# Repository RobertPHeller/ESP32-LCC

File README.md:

# ESP32-LCC

This is a collection of Model Railroad open hardware and open source projects,
using LCC /  OpenMRNIDF, for the ESP32 family of MCUs

These projects were created using Kicad 2013.06.11
(https://launchpad.net/kicad) under CentOS 6 and Kicad 4.0.7 under Ubuntu
18.04. Each subdirectory is one project, and contains a schematic and PCB
design or contains a program for one (or more) projects. There is also
software for the boards using OpenMRNIDF (C++ library for OpenLCB/LCC) for these
projects.

There is a README in each project dir.

1. [ESP32-16LedDriver](https://github.com/RobertPHeller/RPi-RRCircuits/tree/master/ESP32-16LedDriver)

    > 16 on/off LED Driver board using a MCP23017.

1. [ESP32-16PWMLedDriver](https://github.com/RobertPHeller/RPi-RRCircuits/tree/master/ESP32-16PWMLedDriver)

    > 16 LED PWM driver board using a PCA9685.

1. [ESP32-16xDCCOD](https://github.com/RobertPHeller/RPi-RRCircuits/tree/master/ESP32-16xDCCOD)

    > Backplane for up to 16 DCCOD_SMD's using a ESP32 MCU.  Meant as a thought 
    > experiment to see what this would cost, etc.

1. [ESP32-D0WD-V3-MultiFunctionOpenMRNIDF](https://github.com/RobertPHeller/RPi-RRCircuits/tree/master/ESP32-D0WD-V3-MultiFunctionOpenMRNIDF)

    > 

1. [ESP32-HalfSiding](https://github.com/RobertPHeller/RPi-RRCircuits/tree/master/ESP32-HalfSiding)

    > First draft of a ESP32 HalfSiding node using a MCP23017 on/off signal lamps.

1. [ESP32-MultiFunction](https://github.com/RobertPHeller/RPi-RRCircuits/tree/master/ESP32-MultiFunction)

    > This is a circuit board that supports an ESP32 Dev Kit board or TTGO-T1 board
    > to manage a range of possible interlocking plants or other model railroad
    > situations. It contains four stall motor drivers with point sense, four CT
    > Coil type occupancy detectors, four Schmitt-Trigger inputs (for push buttons),
    > four driver outputs, and 16 PWM LED drivers.

1. [ESP32-PWMHalfSiding](https://github.com/RobertPHeller/RPi-RRCircuits/tree/master/ESP32-PWMHalfSiding)

    > This is a circuit board that supports an ESP32 Dev Kit board or TTGO-T1 board 
    > to manage one half (one end) of a siding.  This board can also be used to 
    > manage two bi-directional single track ABS blocks or one bi-directional dual 
    > track ABS block.  There are other trackwork cases this board can handle as 
    > well.  

1. [ESP32-PWMHalfSidingSMD](https://github.com/RobertPHeller/RPi-RRCircuits/tree/master/ESP32-PWMHalfSidingSMD)

    > This is a circuit board that supports an ESP32 Dev Kit board or TTGO-T1 board 
    > to manage one half (one end) of a siding.  This board can also be used to 
    > manage two bi-directional single track ABS blocks or one bi-directional dual 
    > track ABS block.  There are other trackwork cases this board can handle as 
    > well.  

1. [ESP32-S3-MultiFunction](https://github.com/RobertPHeller/RPi-RRCircuits/tree/master/ESP32-S3-MultiFunction)

    > This is a LCC node circuit board that is based around an Espressif ESP32-S3FN8
    > MCU to manage and operate a collection of model railroad sensors and
    > actuators. 

1. [ESP32-S3-MultiFunctionOpenMRNIDF](https://github.com/RobertPHeller/RPi-RRCircuits/tree/master/ESP32-S3-MultiFunctionOpenMRNIDF)

    > 

1. [ESP32_mini_KiCad_Library](https://github.com/RobertPHeller/RPi-RRCircuits/tree/master/ESP32_mini_KiCad_Library)

    > KiCad symbol and footprint for the ESP32 Mini, the ESP32 clone of the Wemos D1 mini with more pins and more power!
    > There is some info on the boards [here](https://www.reddit.com/r/esp8266/comments/a93raj/wemos_ttgo_mini_d1_esp32/). It seems to be a Wemos clone, but is def. not made by them. I really like the boards for the small size and cheap price while giving me the power of an ESP32 and much more IO compared to the Wemos D1 mini.

1. [ESP32ABSBoard](https://github.com/RobertPHeller/RPi-RRCircuits/tree/master/ESP32ABSBoard)

    > ESP32 ABS (Automatic Block Signal) board.  Very simple board: one block 
    > detector, 8 LED drivers.

1. [ESP32BaseBoard](https://github.com/RobertPHeller/RPi-RRCircuits/tree/master/ESP32BaseBoard)

    > ESP32 Base board.  Base starting point for a ESP32 node.

1. [ESP32MRNSketches](https://github.com/RobertPHeller/RPi-RRCircuits/tree/master/ESP32MRNSketches)

    > ESP32 Arduino / OpenMRNLite sketches for the ESP32 boards.

1. [ESP32QuadOCDect](https://github.com/RobertPHeller/RPi-RRCircuits/tree/master/ESP32QuadOCDect)

    > ESP32 Quad Occupancy Detector node.

1. [ESP32QuadSMCSense](https://github.com/RobertPHeller/RPi-RRCircuits/tree/master/ESP32QuadSMCSense)

    > ESP32 Quad Stall Motor w/ sense node.

1. [OpenMRNIDF](https://github.com/RobertPHeller/RPi-RRCircuits/tree/master/OpenMRNIDF)

    > This is an exported version of the OpenMRN library for the ESP32 which is
    > usable as an ESP-IDF component.

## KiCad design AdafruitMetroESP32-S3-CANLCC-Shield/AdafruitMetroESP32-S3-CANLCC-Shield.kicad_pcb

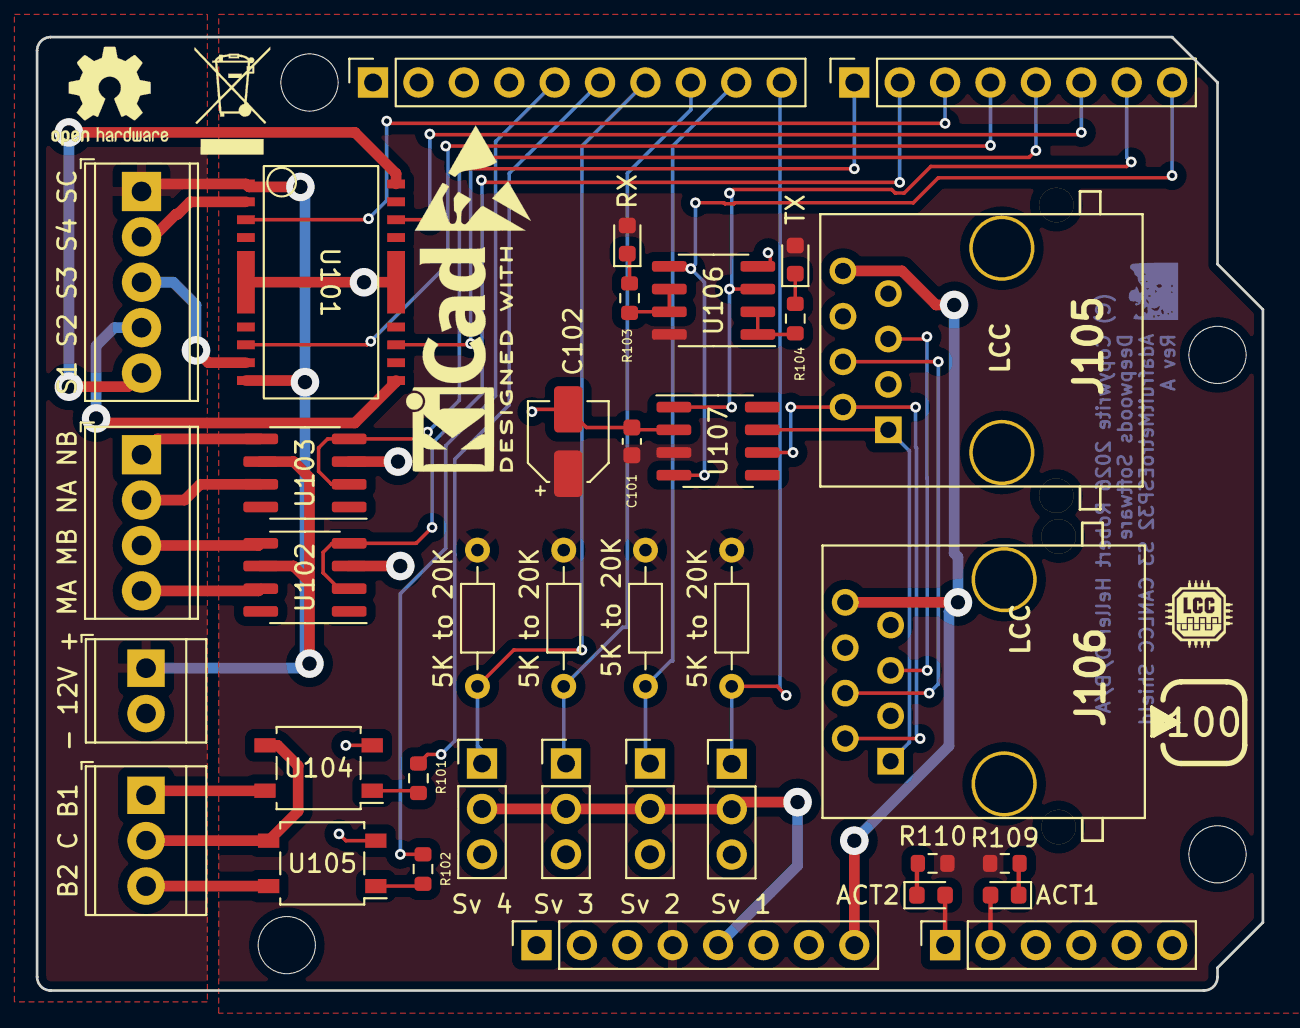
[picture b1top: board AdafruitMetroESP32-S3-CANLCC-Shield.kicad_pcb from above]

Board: 2 copper layers, 68.6 x 53.3 mm, 41 parts (0 on the bottom side), 44 nets.

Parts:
C101: .1 uf; C_0603_1608Metric
C102: 15 uf 15V; CP_Elec_4x5.7
D101: RX; LED_0603_1608Metric
D102: TX; LED_0603_1608Metric
D103: ACT1; LED_0603_1608Metric
D104: ACT2; LED_0603_1608Metric
J1: Power; PinSocket_1x08_P2.54mm_Vertical
J2: Digital/PWM; PinSocket_1x10_P2.54mm_Vertical
J3: Analog; PinSocket_1x06_P2.54mm_Vertical
J4: Digital/PWM; PinSocket_1x08_P2.54mm_Vertical
J101: MA MB NA NB; TerminalBlock_Phoenix_MPT-0,5-4-2.54_1x04_P2.54mm_Horizontal
J102: S1 S2 S3 S4 SC; TerminalBlock_Phoenix_MPT-0,5-5-2.54_1x05_P2.54mm_Horizontal
J103: - 12V +; TerminalBlock_TE_282834-2_1x02_P2.54mm_Horizontal
J104: B2 C B1; TerminalBlock_TE_282834-3_1x03_P2.54mm_Horizontal
J105, J106: LCC; RJ45_8N-S
J107: Sv 4; PinHeader_1x03_P2.54mm_Vertical
J108: Sv 3; PinHeader_1x03_P2.54mm_Vertical
J109: Sv 2; PinHeader_1x03_P2.54mm_Vertical
J110: Sv 1; PinHeader_1x03_P2.54mm_Vertical
MH1, MH2, MH3, MH4: MountingHole_3.2mm
R101, R102: 330; R_0603_1608Metric
R103, R104, R109, R110: 130; R_0603_1608Metric
R105, R106, R107, R108: 5K to 20K; R_Axial_DIN0204_L3.6mm_D1.6mm_P7.62mm_Horizontal
U101: TBD62064AFG; HSOP16-P-300-1.00
U102, U103: TC4428; SOIC-8_3.9x4.9mm_P1.27mm
U104, U105: G3VM-61VY4; SO-4_4.4x4.3mm_P2.54mm
U106: LM358; SOIC-8_3.9x4.9mm_P1.27mm
U107: TCAN332DR; SOIC-8_3.9x4.9mm_P1.27mm

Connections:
+3V3: C101.1, C102.1, D101.2 (A), D102.2 (A), J1.4, R105.1, R106.1, R107.1, R108.1, R109.1, R110.1, U106.8 (V+), U107.3 (Vcc)
+5V: J1.5, J107.2, J108.2, J109.2, J110.2
+12V: J102.1, J103.1, U101.1 (OC), U101.8 (OC), U102.6 (Vdd), U103.6 (Vdd)
/2: J4.6, U101.14 (In)
/4: J4.4, U101.6 (In)
/7: J4.1, U103.2 (IN), U103.4 (IN)
/8: J2.10, J110.1, R108.2
/12: J2.6, R101.2
/13: J2.5, R102.2
/*3: J4.5, U101.11 (In)
/*5: J4.3, U101.3 (In)
/*6: J4.2, U102.2 (IN), U102.4 (IN)
/*9: J2.9, J109.1, R107.2
/*10: J2.8, J108.1, R106.2
/*11: J2.7, J107.1, R105.2
/A0: D104.2 (A), J3.1
/A1: D103.2 (A), J3.2
/CAN_RX: J4.8, U106.5 (+), U107.4 (R)
/CAN_TX: J4.7, U106.3 (+), U107.1 (D)
GND: C101.2, C102.2, J1.6, J1.7, J2.4, J103.2, J105.3, J105.6, J105.7, J106.3, J106.6, J106.7, J107.3, J108.3, J109.3, J110.3, U101.FIN (GND), U102.3 (GND), U103.3 (GND), U104.2, U105.2, U106.4 (V-), U107.2 (GND)
unnamed: D101.1 (K), R103.1
unnamed: D102.1 (K), R104.1
unnamed: D103.1 (K), R109.2
unnamed: D104.1 (K), R110.2
unnamed: J101.1, U103.5 (Out)
unnamed: J101.2, U103.7 (Out)
unnamed: J101.3, U102.5 (Out)
unnamed: J101.4, U102.7 (Out)
unnamed: J102.2, U101.2 (Out)
unnamed: J102.3, U101.7 (Out)
unnamed: J102.4, U101.9 (Out)
unnamed: J102.5, U101.16 (Out)
unnamed: J104.1, U104.4
unnamed: J104.2, U104.3, U105.3
unnamed: J104.3, U105.4
unnamed: J105.1, J106.1, U107.7 (CANH)
unnamed: J105.2, J106.2, U107.6 (CANL)
unnamed: J105.4, J106.4
unnamed: J105.5, J106.5
unnamed: R101.1, U104.1
unnamed: R102.1, U105.1
unnamed: R103.2, U106.6 (-), U106.7
unnamed: R104.2, U106.1, U106.2 (-)
VCC: J1.8, J105.8, J106.8

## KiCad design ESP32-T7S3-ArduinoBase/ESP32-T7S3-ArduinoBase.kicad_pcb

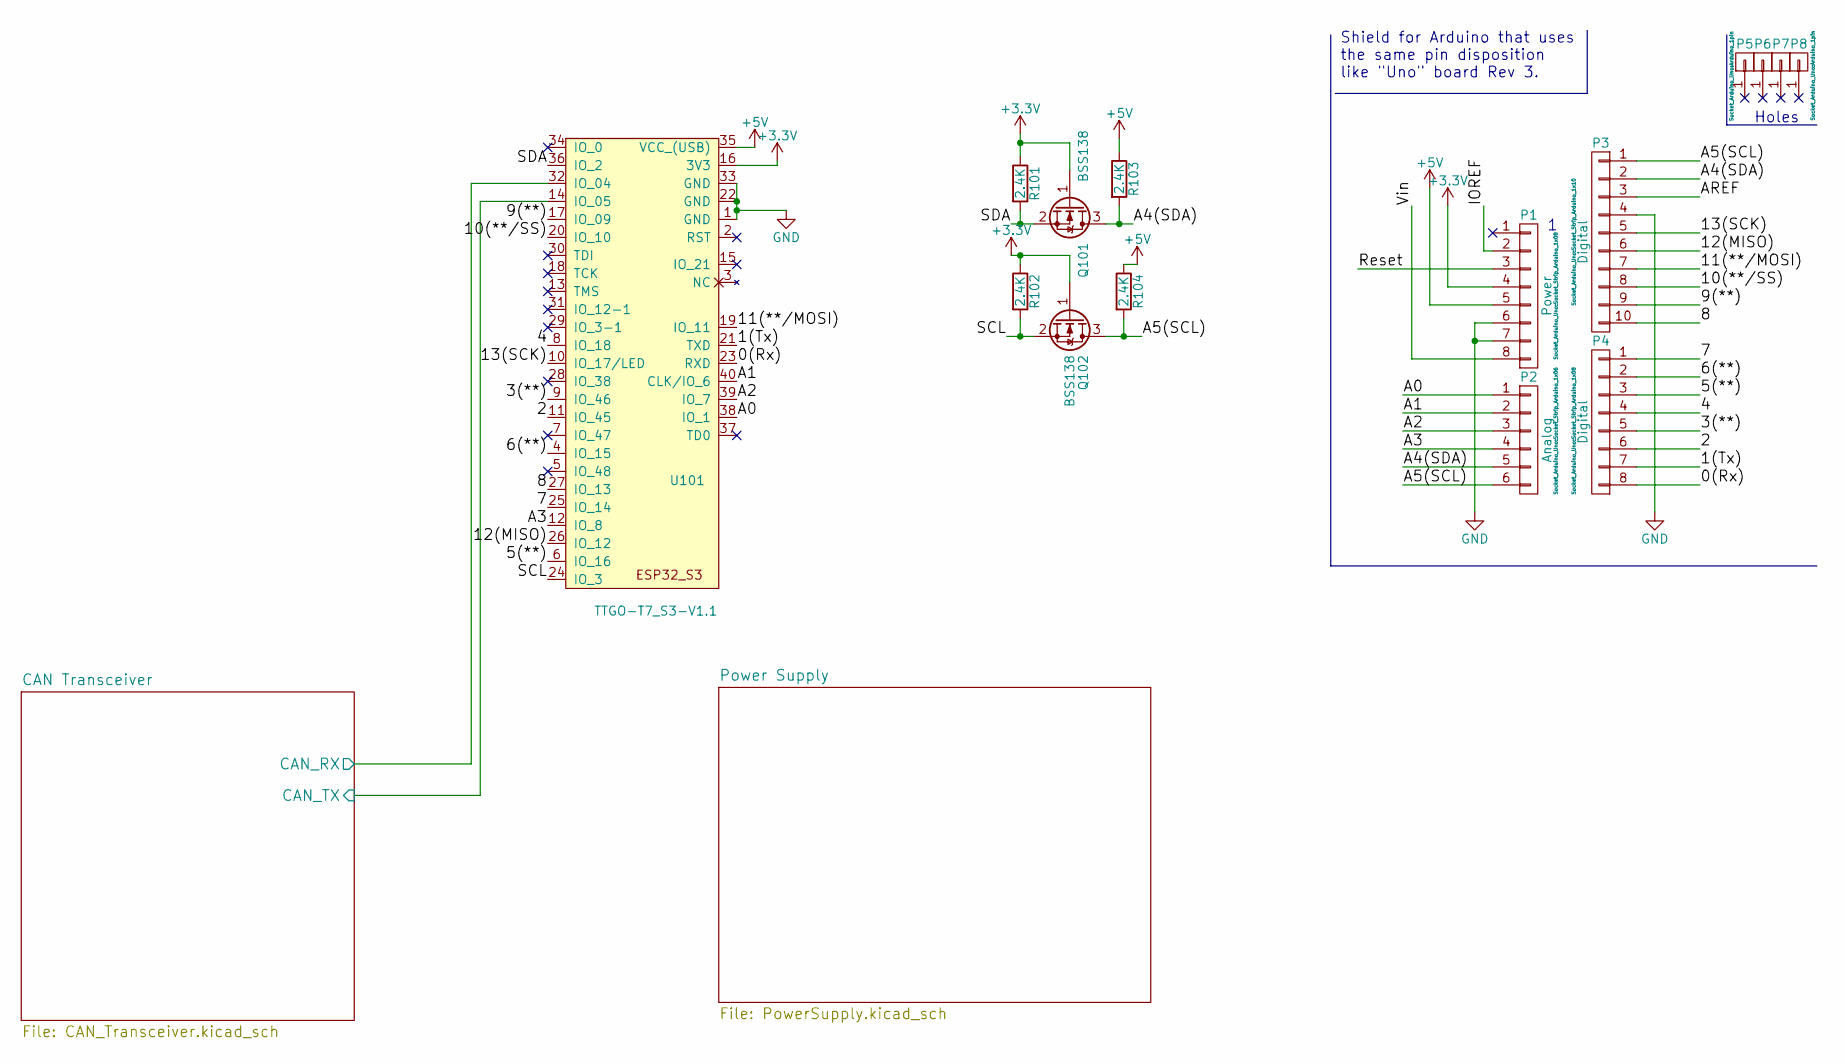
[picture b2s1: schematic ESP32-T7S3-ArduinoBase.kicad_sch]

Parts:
P1: Power; Socket_Strip_Arduino_1x08
P2: Analog; Socket_Strip_Arduino_1x06
P3: Digital; Socket_Strip_Arduino_1x10
P4: Digital; Socket_Strip_Arduino_1x08
P5, P6, P7, P8: CONN_01X01; Arduino_1pin
Q101, Q102: BSS138; SOT-23; Mouser Part Number 621-BSS138-7-F
R101, R102, R103, R104: 2.4K; R_0603
U101: TTGO-T7_S3-V1.1; ESP32_mini

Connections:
+5V: P1.5, R103.1, R104.1, U101.35 (VCC_(USB)); also elsewhere on the board
/0(Rx): P4.8, U101.23 (RXD)
/1(Tx): P4.7, U101.21 (TXD)
/2: P4.6, U101.11 (IO_45)
/3(**): P4.5, U101.9 (IO_46)
/4: P4.4, U101.8 (IO_18)
/5(**): P4.3, U101.6 (IO_16)
/6(**): P4.2, U101.4 (IO_15)
/7: P4.1, U101.25 (IO_14)
/8: P3.10, U101.27 (IO_13)
/9(**): P3.9, U101.17 (IO_09)
/10(**/SS): P3.8, U101.20 (IO_10)
/11(**/MOSI): P3.7, U101.19 (IO_11)
/12(MISO): P3.6, U101.26 (IO_12)
/13(SCK): P3.5, U101.10 (IO_17/LED)
/A0: P2.1, U101.38 (IO_1)
/A1: P2.2, U101.40 (CLK/IO_6)
/A2: P2.3, U101.39 (IO_7)
/A3: P2.4, U101.12 (IO_8)
/A4(SDA): P2.5, P3.2, Q101.3 (D), R103.2
/A5(SCL): P2.6, P3.1, Q102.3 (D), R104.2
/AREF: P3.3
/CAN Transceiver/CAN_RX: U101.32 (IO_04); also elsewhere on the board
/CAN Transceiver/CAN_TX: U101.14 (IO_05); also elsewhere on the board
/IOREF: P1.2
/Reset: P1.3
/SCL: Q102.2 (S), R102.2, U101.24 (IO_3)
/SDA: Q101.2 (S), R101.2, U101.36 (IO_2)
/Vin: P1.8
GND: P1.6, P1.7, P3.4, U101.1 (GND), U101.22 (GND), U101.33 (GND); also elsewhere on the board

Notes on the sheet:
Shield for Arduino that uses the same pin disposition like "Uno" board Rev 3.
Holes

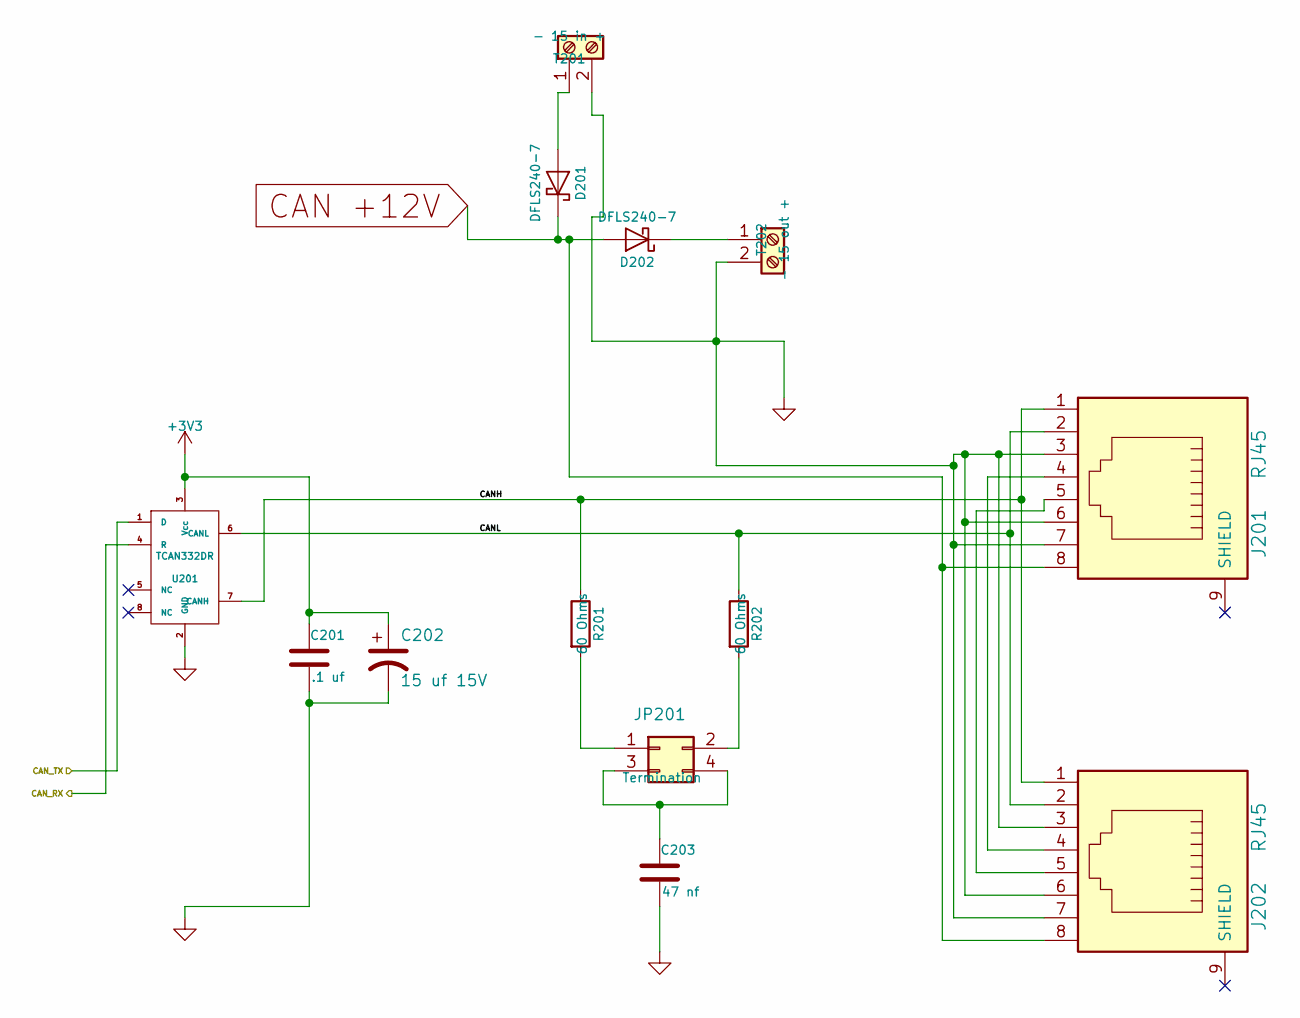
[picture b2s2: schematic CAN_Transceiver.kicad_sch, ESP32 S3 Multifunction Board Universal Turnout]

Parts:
C201: .1 uf; C_0603; Mouser Part Number 710-885012206095
C202: 15 uf 15V; CP_Elec_4x5.7; Mouser Part Number 647-UUD1C150MCL
C203: 47 nf; C_0603; Mouser Part Number 710-885012206093
D201, D202: DFLS240-7; D_PowerDI-123; Mouser Part Number 621-DFLS240-7
J201, J202: RJ45; RJ45_8N-S; Mouser Part Number 710-615008144221
JP201: Termination; Pin_Header_Straight_2x02_Pitch2.54mm; Mouser Part Number 649-67997-404HLF
R201, R202: 60 Ohms; R_1206; Mouser Part Number 71-CRCW120660R0KNAIF
T201: - 15 in +; TerminalBlock_Pheonix_MPT-2.54mm_2pol; Mouser Part Number 651-1725656
T202: - 15 out +; TerminalBlock_Pheonix_MPT-2.54mm_2pol; Mouser Part Number 651-1725656
U201: TCAN332DR; SOIC-8_3.9x4.9mm_Pitch1.27mm; Mouser Part Number 595-TCAN332DR

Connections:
/CAN Transceiver/CANH: J201.1, J202.1, R201.1, U201.7 (CANH)
/CAN Transceiver/CANL: J201.2, J202.2, R202.1, U201.6 (CANL)
/CAN Transceiver/CAN_RX: U201.4 (R); also elsewhere on the board
/CAN Transceiver/CAN_TX: U201.1 (D); also elsewhere on the board
CAN +12V: D201.1 (K), D202.2 (A), J201.8, J202.8; also elsewhere on the board
GND: C201.2, C202.2, C203.2, J201.3, J201.6, J201.7, J202.3, J202.6, J202.7, T201.2, T202.2, U201.2 (GND); also elsewhere on the board
unnamed: C203.1, JP201.3, JP201.4
unnamed: D201.2 (A), T201.1
unnamed: D202.1 (K), T202.1
unnamed: J201.4, J202.4
unnamed: J201.5, J202.5
unnamed: JP201.1, R201.2
unnamed: JP201.2, R202.2

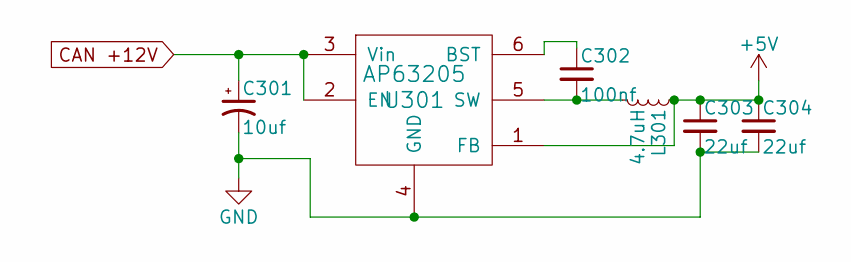
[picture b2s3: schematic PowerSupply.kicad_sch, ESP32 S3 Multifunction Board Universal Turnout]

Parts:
C301: 10uf; CP_Elec_5x5.3; Mouser Part Number 710-865230542002
C302: 100nf; C_0603; Mouser Part Number 710-885012206020
C303, C304: 22uf; C_0603; Mouser Part Number 603-CC0603MRX6S5B226
L301: 4.7uH; L_7.3x7.3_H4.5; Mouser Part Number 81-B1047AS-4R7NP3
U301: AP63205; TSOT-23-6_MK06A; Mouser Part Number 621-AP63205WU-7

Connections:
+5V: C303.1, C304.1, L301.1, U301.1 (FB); also elsewhere on the board
CAN +12V: C301.1, U301.2 (EN), U301.3 (Vin); also elsewhere on the board
GND: C301.2, C303.2, C304.2, U301.4 (GND); also elsewhere on the board
unnamed: C302.1, U301.6 (BST)
unnamed: C302.2, L301.2, U301.5 (SW)

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
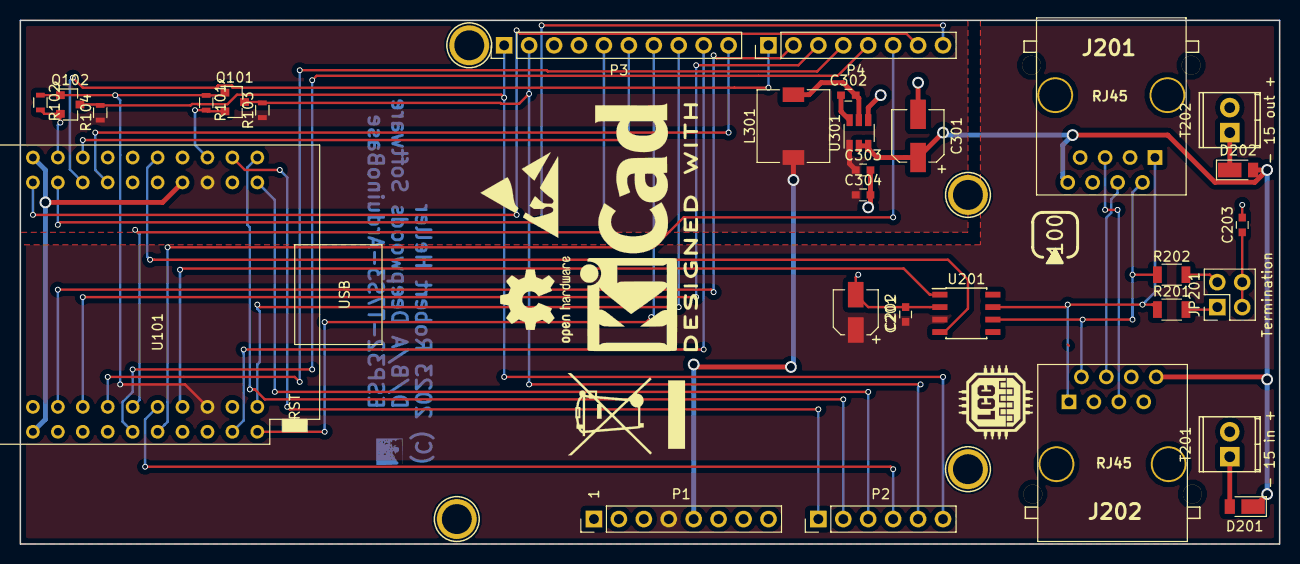
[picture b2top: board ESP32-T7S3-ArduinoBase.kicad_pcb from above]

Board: 2 copper layers, 128.3 x 53.3 mm, 34 parts (0 on the bottom side), 39 nets.

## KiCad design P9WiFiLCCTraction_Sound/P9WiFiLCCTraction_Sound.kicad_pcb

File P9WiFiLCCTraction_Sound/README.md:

# JST 9-Pin WiFi LCC Traction Node 

This is a WiFi LCC Traction Node that has a DCC standard JST 9-pin connecter.

It has support for 4 function outputs.

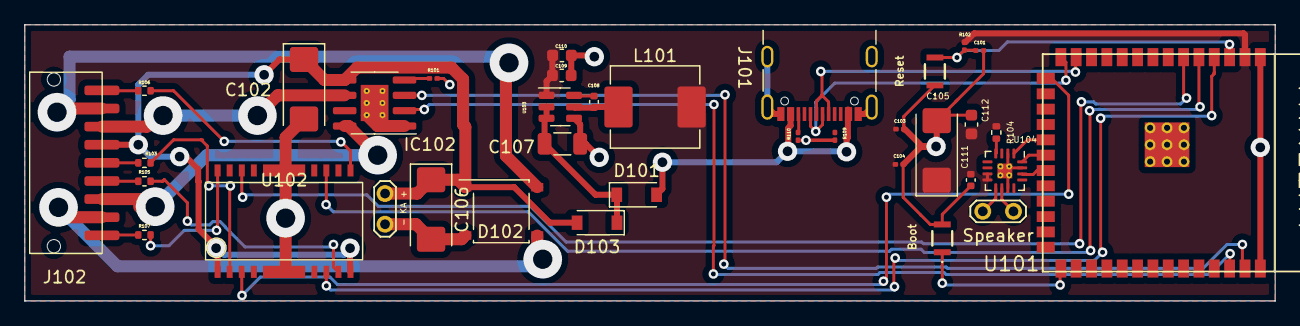
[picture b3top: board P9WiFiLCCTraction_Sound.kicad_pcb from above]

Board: 2 copper layers, 103.5 x 22.9 mm, 36 parts (0 on the bottom side), 38 nets.

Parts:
C101, C103, C104: 1uf; C_0201_0603Metric
C102, C105: 10uf 25V; CP_EIA-6032-28_Kemet-C
C106: 100Uf 16V; CP_EIA-6032-28_Kemet-C
C107: 10uf 25V; C_1206_3216Metric
C108: 100nf; C_0402_1005Metric
C109, C110: 22uf 6.3V; C_0603_1608Metric
C111: .1uf; C_0402_1005Metric
C112: 10uf 6.3V; C_0603_1608Metric
D101, D103: SBR545SAFQ-13; D_SOD-123
D102: ABS15M; Diode_Bridge_Diotec_ABS
IC102: MP6614GN-Z; SOIC-8-1EP_3.9x4.9mm_P1.27mm_EP2.29x3mm_ThermalVias
J101: USB_C_Receptacle; USB_C_Receptacle_GCT_USB4105-xx-A_16P_TopMnt_Horizontal
J102: DCC 9-pin; JST_ZH_S9B-ZR-SM4A-TF_1x09-1MP_P1.50mm_Horizontal
L101: 3.9uH; L_Abracon_ASPI-0630LR
R101: 20K; R_0201_0603Metric
R102, R109, R110: 5.1K; R_0201_0603Metric
R103, R105, R106, R107: 1K; R_0402_1005Metric
R104: 0; R_0402_1005Metric
SW101: Reset; NanoT160AS
SW102: Boot; NanoT160AS
TP101: Speaker; TestPoint_2Pads_Pitch2.54mm_Drill0.8mm
TP104: - KA +; TestPoint_2Pads_Pitch2.54mm_Drill0.8mm
U101: ESP32_S3_WROOM; ESP32_S3_WROOM-1
U102: TBD62064AFG_1; HSOP16-P-300-1.00
U103: AP63203WU; TSOT-23-6
U104: MAX98357AETE+T; TQFN-16-1EP_3x3mm_P0.5mm_EP1.23x1.23mm_ThermalVias

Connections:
+3V3: C103.1, C104.1, C105.1, C109.1, C110.1, C111.1, C112.1, L101.2, R102.1, R104.1, U101.2 (3v3), U103.1 (FB), U104.7 (VDD_1), U104.8 (VDD_2)
/Boot0: SW102.1, U101.27 (IO0)
/D+: J101.A6 (D+), J101.B6 (D+), U101.14 (IO20)
/D-: J101.A7 (D-), J101.B7 (D-), U101.13 (IO19)
/Function1: U101.15 (IO3), U102.3 (In)
/Function2: U101.4 (IO4), U102.6 (In)
/Function3: U101.5 (IO5), U102.11 (In)
/Function4: U101.6 (IO6), U102.14 (In)
/I2S_BCLK: U101.20 (IO12), U104.16 (BCLK)
/I2S_TX: U101.19 (IO11), U104.1 (DIN)
/LRCLK: U101.21 (IO13), U104.14 (LRCLK)
/Left Rail: D102.3, J102.2
/MForward: IC102.3 (IN1), U101.39 (IO1)
/MReverse: IC102.2 (IN2), U101.38 (IO2)
/Motor +: IC102.6 (OUT1), J102.7
/Motor -: IC102.8 (OUT2), J102.3
/Out 1: J102.5, R103.1
/Out 2: J102.4, R105.1
/Out 3: J102.9, R106.1
/Out 4: J102.1, R107.1
/Reset: C101.1, R102.2, SW101.2, U101.3 (EN)
/Right Rail: D102.4, J102.8
/VBus: D101.2 (A), J101.A4 (VBUS), J101.A9 (VBUS), J101.B4 (VBUS), J101.B9 (VBUS)
/Vin: C107.1, D101.1 (K), D103.1 (K), U103.2 (EN), U103.3 (IN)
GND: C101.2, C102.2, C103.2, C104.2, C105.2, C106.2, C107.2, C109.2, C110.2, C111.2, C112.2, D102.2 (-), IC102.1 (GND), IC102.9 (EP), J101.A1 (GND), J101.A12 (GND), J101.B1 (GND), J101.B12 (GND), J101.S1 (SHIELD), R101.2, R109.2, R110.2, SW101.1, SW102.2, TP104.1, U101.1 (GND), U101.40 (GND), U101.EPad (GND), U102.FIN (GND), U103.4 (GND), U104.2 (GAIN_SLOT), U104.3 (GND_1), U104.11 (GND_2), U104.15 (GND_3), U104.17 (THERMAL_PAD)
unnamed: C108.1, L101.1, U103.5 (SW)
unnamed: C108.2, U103.6 (BST)
unnamed: IC102.4 (ISET), R101.1
unnamed: J101.A5 (CC1), R109.1
unnamed: J101.B5 (CC2), R110.1
unnamed: R103.2, U102.2 (Out)
unnamed: R104.2, U104.4 (~SD_MODE)
unnamed: R105.2, U102.7 (Out)
unnamed: R106.2, U102.9 (Out)
unnamed: R107.2, U102.16 (Out)
unnamed: TP101.1, U104.9 (OUTP)
unnamed: TP101.2, U104.10 (OUTN)
OC: C102.1, C106.1, D102.1 (+), D103.2 (A), IC102.5 (VIN), J102.6, TP104.2, U102.1 (OC), U102.8 (OC)

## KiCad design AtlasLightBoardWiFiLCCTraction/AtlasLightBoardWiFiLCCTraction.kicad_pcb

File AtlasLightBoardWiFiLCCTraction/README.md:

# Atlas Light Board WiFi LCC Traction Node

This is a WiFi LCC Traction Node that is a drop in replacement for any HO 
diesel loco that has mounting for a DCC decoder like the NCE DA-SR or TCS A4X,
that is the Atlas Light Board DCC decoders.

It has support for 6 function outputs.

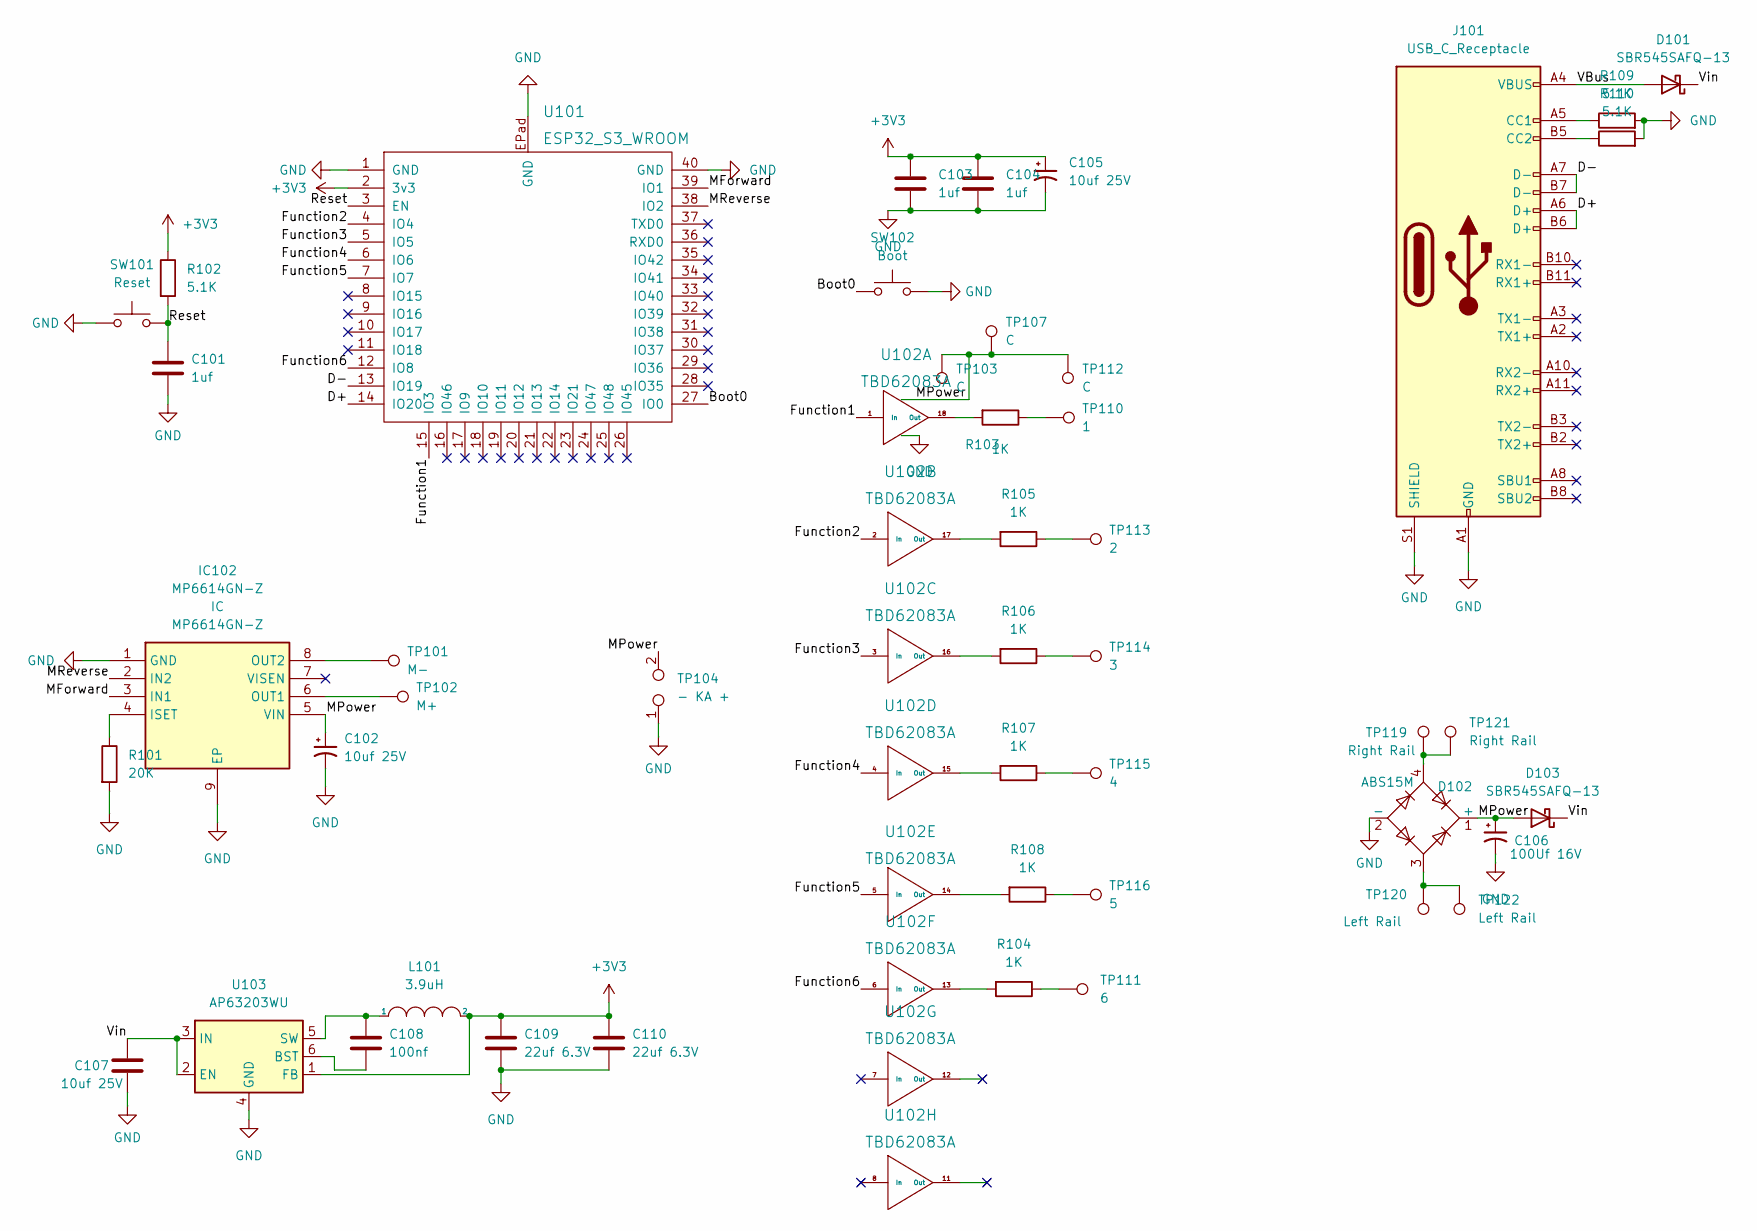
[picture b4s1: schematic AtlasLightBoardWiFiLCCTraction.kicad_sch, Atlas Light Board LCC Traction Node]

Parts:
C101, C103, C104: 1uf; C_0201_0603Metric; Mouser Part Number 81-GRT033R60J105ME3D
C102, C105: 10uf 25V; CP_EIA-6032-28_Kemet-C; Mouser Part Number 80-T491C106K25AT7280
C106: 100Uf 16V; CP_EIA-6032-28_Kemet-C; Mouser Part Number 647-F931C107MCC
C107: 10uf 25V; C_1206_3216Metric; Mouser Part Number 187-CL31B106KAHNNNE
C108: 100nf; C_0402_1005Metric; Mouser Part Number 791-RF15N0R1B250CT
C109, C110: 22uf 6.3V; C_0603_1608Metric; Mouser Part Number 791-0603X226M6R3CT
D101, D103: SBR545SAFQ-13; D_SOD-123; Mouser Part Number 610-CMMSH1-60GTR
D102: ABS15M; Diode_Bridge_Diotec_ABS; Mouser Part Number 637-ABS15M
IC102: MP6614GN-Z; SOIC-8-1EP_3.9x4.9mm_P1.27mm_EP2.29x3mm_ThermalVias; Mouser Part Number 946-MP6614GN-Z
J101: USB_C_Receptacle; USB_C_Receptacle_GCT_USB4105-xx-A_16P_TopMnt_Horizontal; Mouser Part Number 640-USB4105-GF-A
L101: 3.9uH; L_Abracon_ASPI-0630LR; Mouser Part Number 815-ASPI-0628-3R9MT1
R101: 20K; R_0201_0603Metric; Mouser Part Number 603-RC0201JR-0720KL
R102, R109, R110: 5.1K; R_0201_0603Metric; Mouser Part Number 603-RC0201FR-075K1L
R103, R104, R105, R106, R107, R108: 1K; R_0402_1005Metric; Mouser Part Number 603-RC0402JR-7W1KL
SW101: Reset; NanoT160AS; Mouser Part Number 611-NANOT160AS
SW102: Boot; NanoT160AS; Mouser Part Number 611-NANOT160AS
TP101: M-; TestPoint_THTPad_3.0x3.0mm_Drill1.5mm
TP102: M+; TestPoint_THTPad_3.0x3.0mm_Drill1.5mm
TP103: C; TestPoint_THTPad_3.0x3.0mm_Drill1.5mm
TP104: - KA +; TestPoint_2Pads_Pitch2.54mm_Drill0.8mm
TP107: C; TestPoint_Pad_2.0x2.0mm
TP110: 1; TestPoint_THTPad_3.0x3.0mm_Drill1.5mm
TP111: 6; TestPoint_Pad_2.0x2.0mm
TP112: C; TestPoint_THTPad_1.5x1.5mm_Drill0.7mm
TP113: 2; TestPoint_THTPad_1.5x1.5mm_Drill0.7mm
TP114: 3; TestPoint_Pad_2.0x2.0mm
TP115: 4; TestPoint_Pad_2.0x2.0mm
TP116: 5; TestPoint_Pad_2.0x2.0mm
TP119: Right Rail; TestPoint_THTPad_3.0x3.0mm_Drill1.5mm
TP120: Left Rail; TestPoint_THTPad_3.0x3.0mm_Drill1.5mm
TP121: Right Rail; TestPoint_THTPad_1.5x1.5mm_Drill0.7mm
TP122: Left Rail; TestPoint_THTPad_1.5x1.5mm_Drill0.7mm
U101: ESP32_S3_WROOM; ESP32_S3_WROOM-1; Mouser Part Number 356-ESP32-S3WROOM1N4
U102: TBD62083A; SSOP-18_4.4x6.5mm_P0.65mm; Mouser Part Number 757-TBD62083AFNGEL
U103: AP63203WU; TSOT-23-6

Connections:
+3V3: C103.1, C104.1, C105.1, C109.1, C110.1, L101.2, R102.1, U101.2 (3v3), U103.1 (FB)
/Boot0: SW102.1, U101.27 (IO0)
/D+: J101.A6 (D+), J101.B6 (D+), U101.14 (IO20)
/D-: J101.A7 (D-), J101.B7 (D-), U101.13 (IO19)
/Function1: U101.15 (IO3), U102.1 (In)
/Function2: U101.4 (IO4), U102.2 (In)
/Function3: U101.5 (IO5), U102.3 (In)
/Function4: U101.6 (IO6), U102.4 (In)
/Function5: U101.7 (IO7), U102.5 (In)
/Function6: U101.12 (IO8), U102.6 (In)
/MForward: IC102.3 (IN1), U101.39 (IO1)
/MPower: C102.1, C106.1, D102.1 (+), D103.2 (A), IC102.5 (VIN), TP103.1, TP104.2, TP107.1, TP112.1, U102.10 (OC)
/MReverse: IC102.2 (IN2), U101.38 (IO2)
/Reset: C101.1, R102.2, SW101.2, U101.3 (EN)
/VBus: D101.2 (A), J101.A4 (VBUS), J101.A9 (VBUS), J101.B4 (VBUS), J101.B9 (VBUS)
/Vin: C107.1, D101.1 (K), D103.1 (K), U103.2 (EN), U103.3 (IN)
GND: C101.2, C102.2, C103.2, C104.2, C105.2, C106.2, C107.2, C109.2, C110.2, D102.2 (-), IC102.1 (GND), IC102.9 (EP), J101.A1 (GND), J101.A12 (GND), J101.B1 (GND), J101.B12 (GND), J101.S1 (SHIELD), R101.2, R109.2, R110.2, SW101.1, SW102.2, TP104.1, U101.1 (GND), U101.40 (GND), U101.EPad (GND), U102.9 (IC), U103.4 (GND)
unnamed: C108.1, L101.1, U103.5 (SW)
unnamed: C108.2, U103.6 (BST)
unnamed: D102.3, TP120.1, TP122.1
unnamed: D102.4, TP119.1, TP121.1
unnamed: IC102.4 (ISET), R101.1
unnamed: IC102.6 (OUT1), TP102.1
unnamed: IC102.8 (OUT2), TP101.1
unnamed: J101.A5 (CC1), R109.1
unnamed: J101.B5 (CC2), R110.1
unnamed: R103.1, TP110.1
unnamed: R103.2, U102.18 (Out)
unnamed: R104.1, TP111.1
unnamed: R104.2, U102.13 (Out)
unnamed: R105.1, TP113.1
unnamed: R105.2, U102.17 (Out)
unnamed: R106.1, TP114.1
unnamed: R106.2, U102.16 (Out)
unnamed: R107.1, TP115.1
unnamed: R107.2, U102.15 (Out)
unnamed: R108.1, TP116.1
unnamed: R108.2, U102.14 (Out)

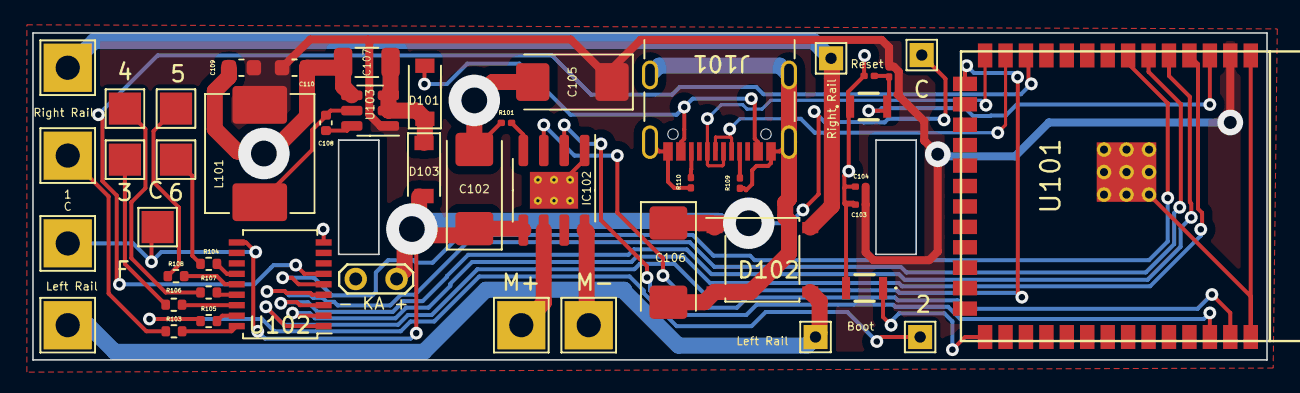
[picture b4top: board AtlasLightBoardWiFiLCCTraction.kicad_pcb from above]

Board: 2 copper layers, 76.7 x 20.3 mm, 47 parts (0 on the bottom side), 38 nets.

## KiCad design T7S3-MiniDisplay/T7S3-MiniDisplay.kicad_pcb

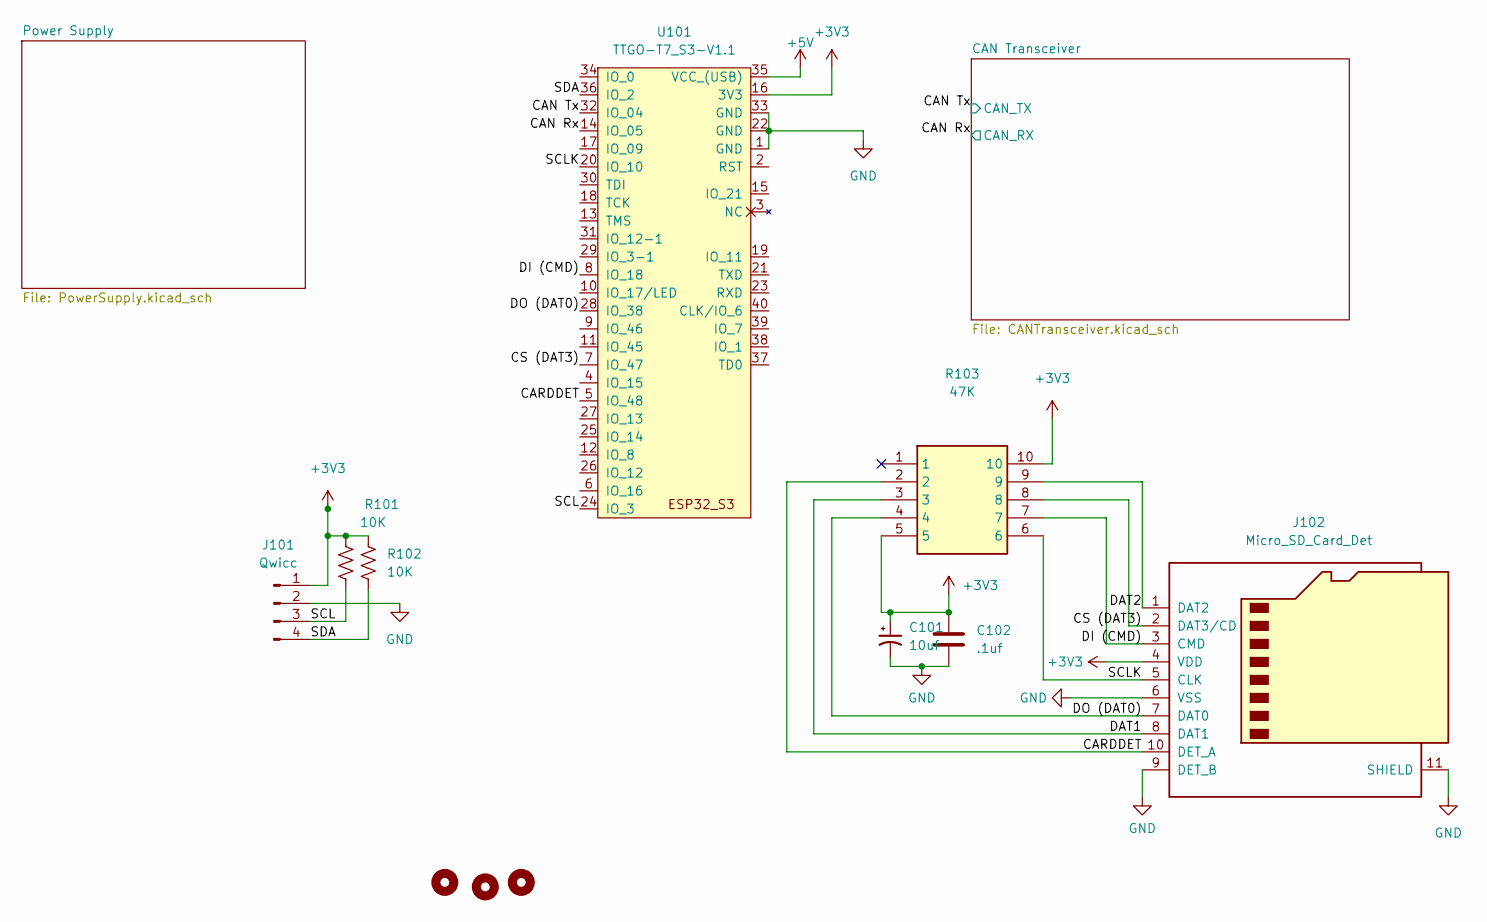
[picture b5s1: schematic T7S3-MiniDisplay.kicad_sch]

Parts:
C101: 10uf; CP_Elec_4x5.7; Mouser Part Number 667-EEE-HB1C100R
C102: .1uf; C_0603_1608Metric; Mouser Part Number 80-C0603C104K5R7411
H101, H102, H103: MountingHole; MountingHole_2.5mm
J101: Qwicc; JST_PH_S4B-PH-SM4-TB_1x04-1MP_P2.00mm_Horizontal; MPN S4B-PH-SM4-TB(LF)(SN); Mouser Part Number 306-S4BPHSM4TBLFSN
J102: Micro_SD_Card_Det; microSD_HC_Hirose_DM3D-SF; Mouser Part Number 798-DM3D-SF
R101, R102: 10K; R_0201_0603Metric; Mouser Part Number 603-RE0603DRE0710KL
R103: 47K; YC158TJR074K7L; Mouser Part Number 603-YC158TJR-0747KL
U101: TTGO-T7_S3-V1.1; ESP32_mini

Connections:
+3V3: C101.1, C102.1, J101.1, J102.4 (VDD), R101.1, R102.1, R103.5, R103.10, U101.16 (3V3); also elsewhere on the board
+5V: U101.35 (VCC_(USB)); also elsewhere on the board
/CAN Rx: U101.14 (IO_05); also elsewhere on the board
/CAN Tx: U101.32 (IO_04); also elsewhere on the board
/CARDDET: J102.10 (DET_A), R103.2, U101.5 (IO_48)
/CS (DAT3): J102.2 (DAT3/CD), R103.8, U101.7 (IO_47)
/DAT1: J102.8 (DAT1), R103.3
/DAT2: J102.1 (DAT2), R103.9
/DI (CMD): J102.3 (CMD), R103.7, U101.8 (IO_18)
/DO (DAT0): J102.7 (DAT0), R103.4, U101.28 (IO_38)
/SCL: J101.3, R101.2, U101.24 (IO_3)
/SCLK: J102.5 (CLK), R103.6, U101.20 (IO_10)
/SDA: J101.4, R102.2, U101.36 (IO_2)
GND: C101.2, C102.2, J101.2, J102.6 (VSS), J102.9 (DET_B), J102.11 (SHIELD), U101.1 (GND), U101.22 (GND), U101.33 (GND); also elsewhere on the board

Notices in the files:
ESP32-Feather-6B6L/ESP32-Feather-6B6L/ESP32-Feather-6B6L.ino:
Copyright (C) 2024  Robert Heller D/B/A Deepwoods Software
This program is free software; you can redistribute it and/or modify
it under the terms of the GNU General Public License as published by
the Free Software Foundation; either version 2 of the License, or
(at your option) any later version.
ESP32-S3-MultiFunctionOpenMRNIDF/main/esp32multifunction.cpp:
Copyright (C) 2022  Robert Heller D/B/A Deepwoods Software
ESP32-Mini32-OctalBuffer/ESP32-Mini32-OctalBuffer.kicad_pcb:
(C) 2023 Robert Heller
